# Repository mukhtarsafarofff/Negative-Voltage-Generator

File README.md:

(ENG) A negative voltage is not fundamentally different from a positive voltage .  Both represent potential energy relative to a reference potential. If a circuit node is at a positive voltage relative to the reference node and when we connect these two nodes with a conductor, conventional current will flow from the positive node to the reference node. Capacitors and inductors are basic electronic components that can store energy, and both can be used to generate negative voltages.  Capacitor-based negative voltage generators belong to the “charge pump” category of power-supply circuits. Inductor-based negative voltage generators belong to the “switch mode” category. Inductor-based solutions, which are also called DC/DC converters and switching power supplies, are much more common. Though many electronic devices accomplish their required functionality without a negative supply voltage, some applications significantly benefit from the presence of a “bipolar” power supply, i.e., a power supply with both positive and negative voltage rails. In this project, i'm  using oscillators, that are based on 555 astable oscillator. In this circuit can be made more efficient as well as increasing the output voltage by using Schottky diodes instead of generic silicon. This is because Schottky diodes  results in a larger negative voltage. The oscillator can be anything from a 555 timer to a microcontroller, but remember that the negative voltage will be equal to the oscillator's max voltage – min voltage.  For example, negative voltages allow sinusoidal signals to extend above and below zero, just as a theoretical sinusoid does, and high-power amplifiers with a bipolar supply don’t need a (potentially expensive) DC-blocking capacitor. 

(DEU)  Eine negative Spannung unterscheidet sich im Grunde nicht von einer positiven Spannung. Beide repräsentieren potentielle Energie relativ zu einem Referenzpotenzial.
Wenn ein Schaltungsknoten eine positive Spannung im Verhältnis zum Referenzknoten hat und wir diese beiden Knoten mit einem Leiter verbinden, fließt der konventionelle Strom vom positiven Knoten zum Referenzknoten. Kondensatoren und Induktivitäten sind grundlegende elektronische Bauteile, die Energie speichern können, und beide können verwendet werden, um negative Spannungen zu erzeugen. Kondensatorbasierte negative Spannungsquellen gehören zur Kategorie der "Ladungspumpen"-Stromversorgungsschaltungen. Induktorbasierte negative Spannungsquellen gehören zur Kategorie des "Schaltmodus". Induktorbasierte Lösungen, die auch als DC/DC-Wandler und Schaltnetzteile bezeichnet werden, sind viel häufiger. Obwohl viele elektronische Geräte ihre erforderliche Funktionalität ohne eine negative Versorgungsspannung erreichen, profitieren einige Anwendungen erheblich von der Anwesenheit einer „bipolaren“ Stromversorgung, d.h. einer Stromversorgung mit sowohl positiven als auch negativen Spannungsschienen.  In dieser Schaltung kann durch die Verwendung von Schottky-Dioden anstelle von generischem Silizium. Zum Beispiel ermöglichen negative Spannungen, dass sinusförmige Signale sich über und unter null erstrecken, so wie es eine theoretische Sinuskurve tut, und Hochleistungsverstärker mit einer bipolaren Stromversorgung benötigen keinen (potenziell teuren) Gleichstromsperrkondensator.  Auf diese weise erzielt  eine höhere Effizienz  und die Ausgangsspannung erhöht werden. Der Oszillator kann alles Mögliche sein, von einem 555-Timer bis zu einem Mikrocontroller, aber denken Sie daran, dass die negative Spannung gleich der Differenz zwischen der maximalen und minimalen Spannung des Oszillators ist.  In diesem Projekt verwende ich Oszillatoren, die auf dem 555 astabilen Oszillator basieren.

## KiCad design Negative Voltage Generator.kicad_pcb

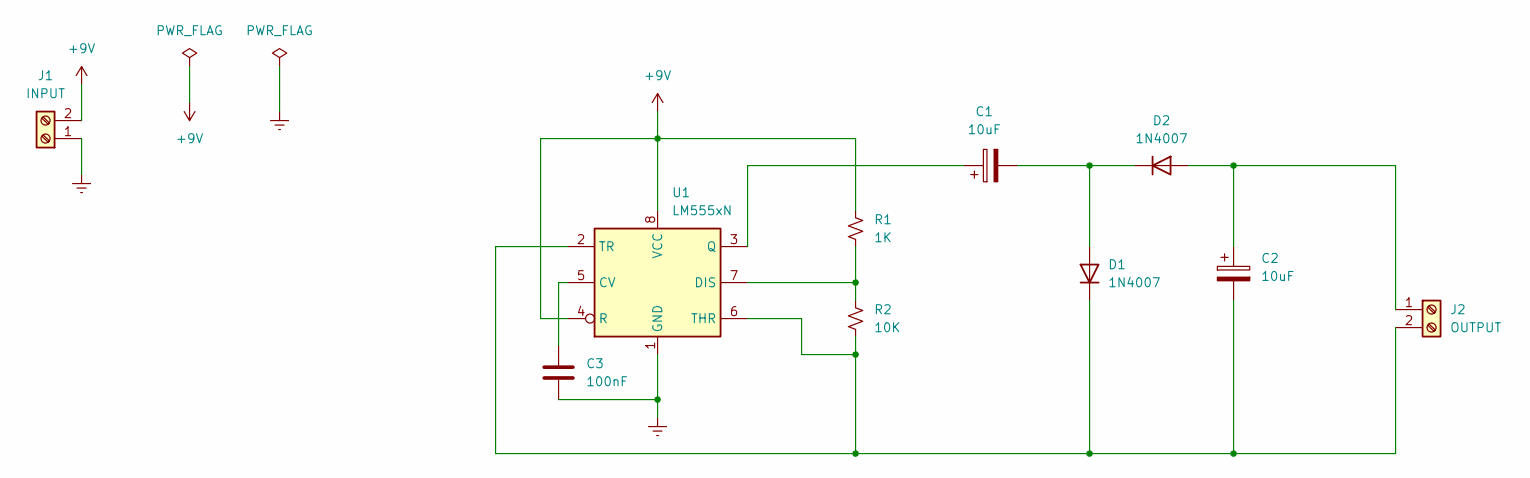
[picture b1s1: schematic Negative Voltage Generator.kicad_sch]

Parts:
C1, C2: 10uF; CP_Radial_D13.0mm_P7.50mm
C3: 100nF; C_Disc_D8.0mm_W5.0mm_P7.50mm
D1, D2: 1N4007; D_DO-41_SOD81_P10.16mm_Horizontal
J1: INPUT; TerminalBlock_bornier-2_P5.08mm
J2: OUTPUT; TerminalBlock_bornier-2_P5.08mm
R1: 1K; R_Axial_DIN0309_L9.0mm_D3.2mm_P15.24mm_Horizontal
R2: 10K; R_Axial_DIN0309_L9.0mm_D3.2mm_P15.24mm_Horizontal
U1: LM555xN; DIP-8_W7.62mm

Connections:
+9V: J1.2, R1.2, U1.4 (R), U1.8 (VCC)
Earth: C3.2, J1.1, U1.1 (GND)
unnamed: C1.2, D1.2 (A), D2.1 (K)
unnamed: C2.2, D1.1 (K), J2.2, R2.1, U1.2 (TR), U1.6 (THR)
unnamed: C2.1, D2.2 (A), J2.1
unnamed: C3.1, U1.5 (CV)
unnamed: R1.1, R2.2, U1.7 (DIS)
unnamed: C1.1, U1.3 (Q)

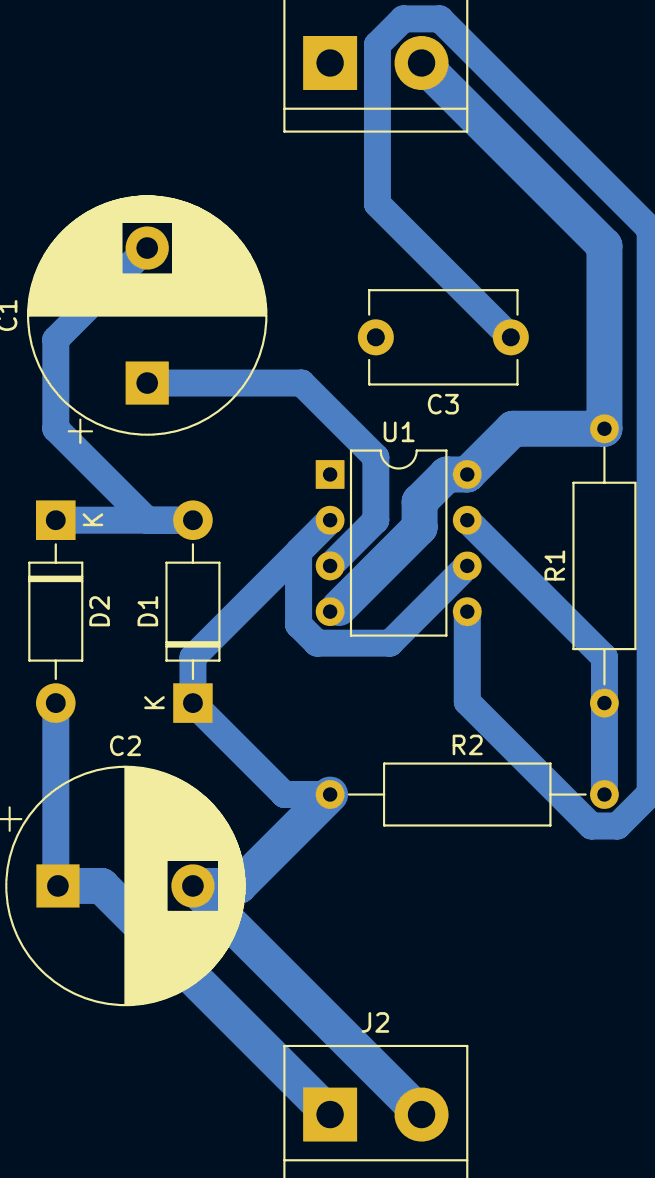
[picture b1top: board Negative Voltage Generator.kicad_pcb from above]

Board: 2 copper layers, 10 parts (0 on the bottom side), 8 nets.

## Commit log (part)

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2024-03-18 Negative Voltage Generator is accomplished
2024-03-25 Negative Voltage Generator is renewed
